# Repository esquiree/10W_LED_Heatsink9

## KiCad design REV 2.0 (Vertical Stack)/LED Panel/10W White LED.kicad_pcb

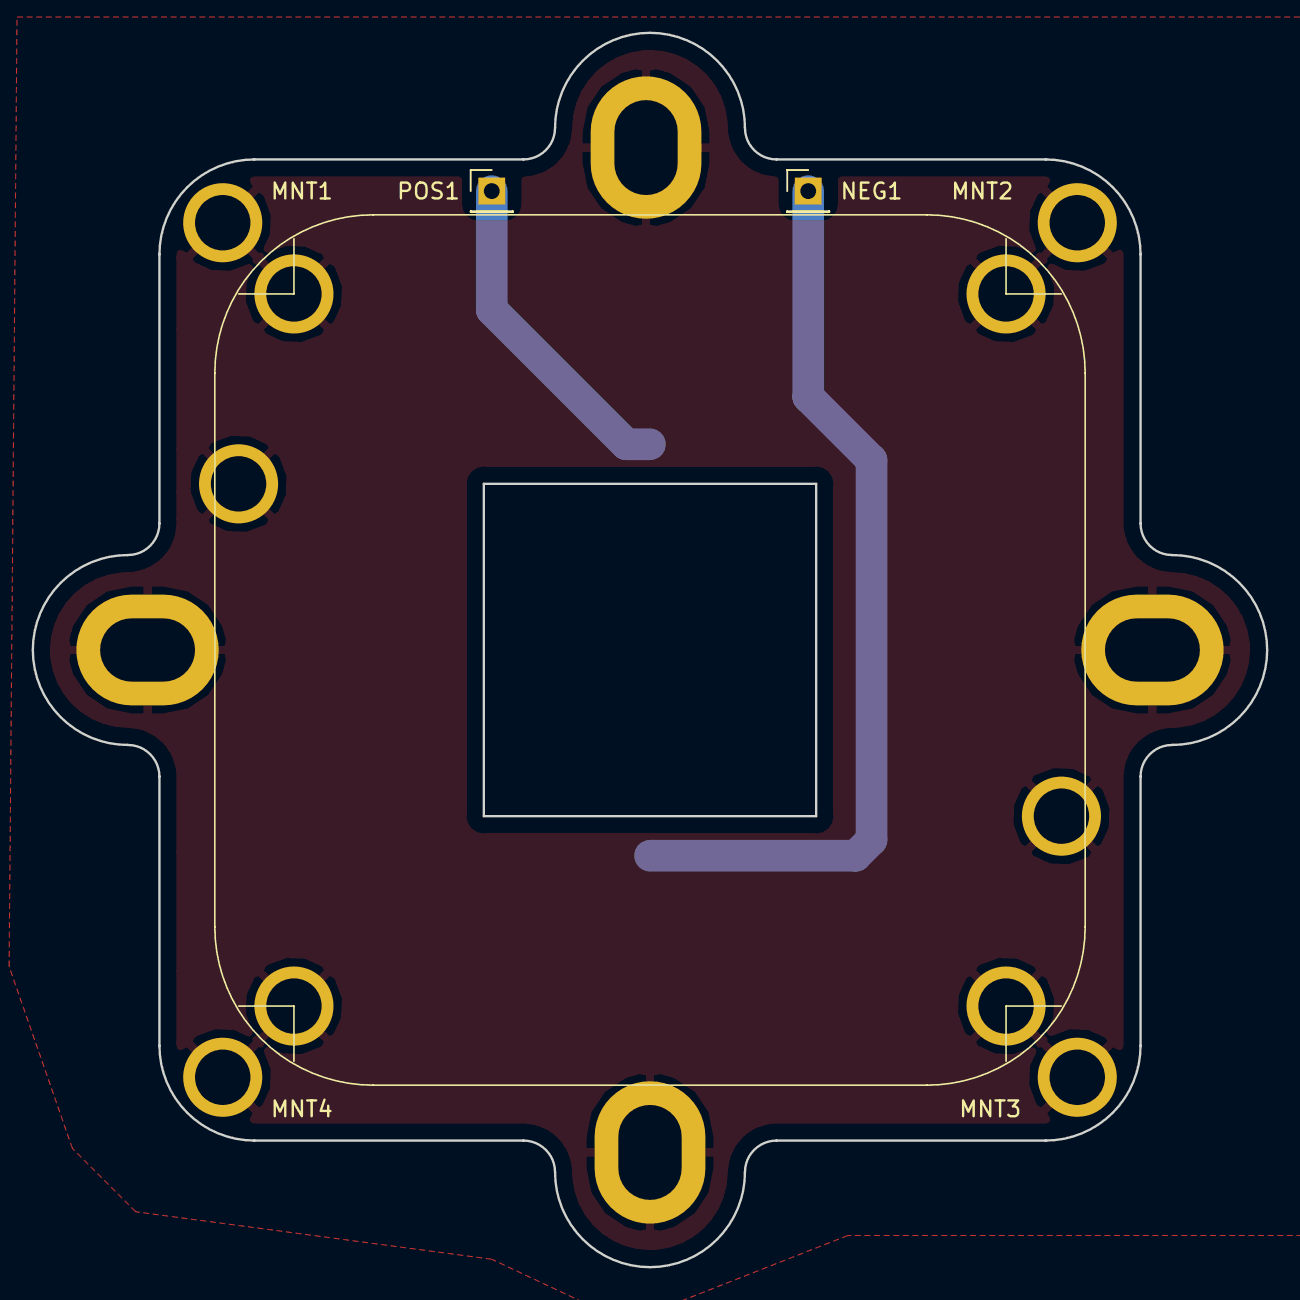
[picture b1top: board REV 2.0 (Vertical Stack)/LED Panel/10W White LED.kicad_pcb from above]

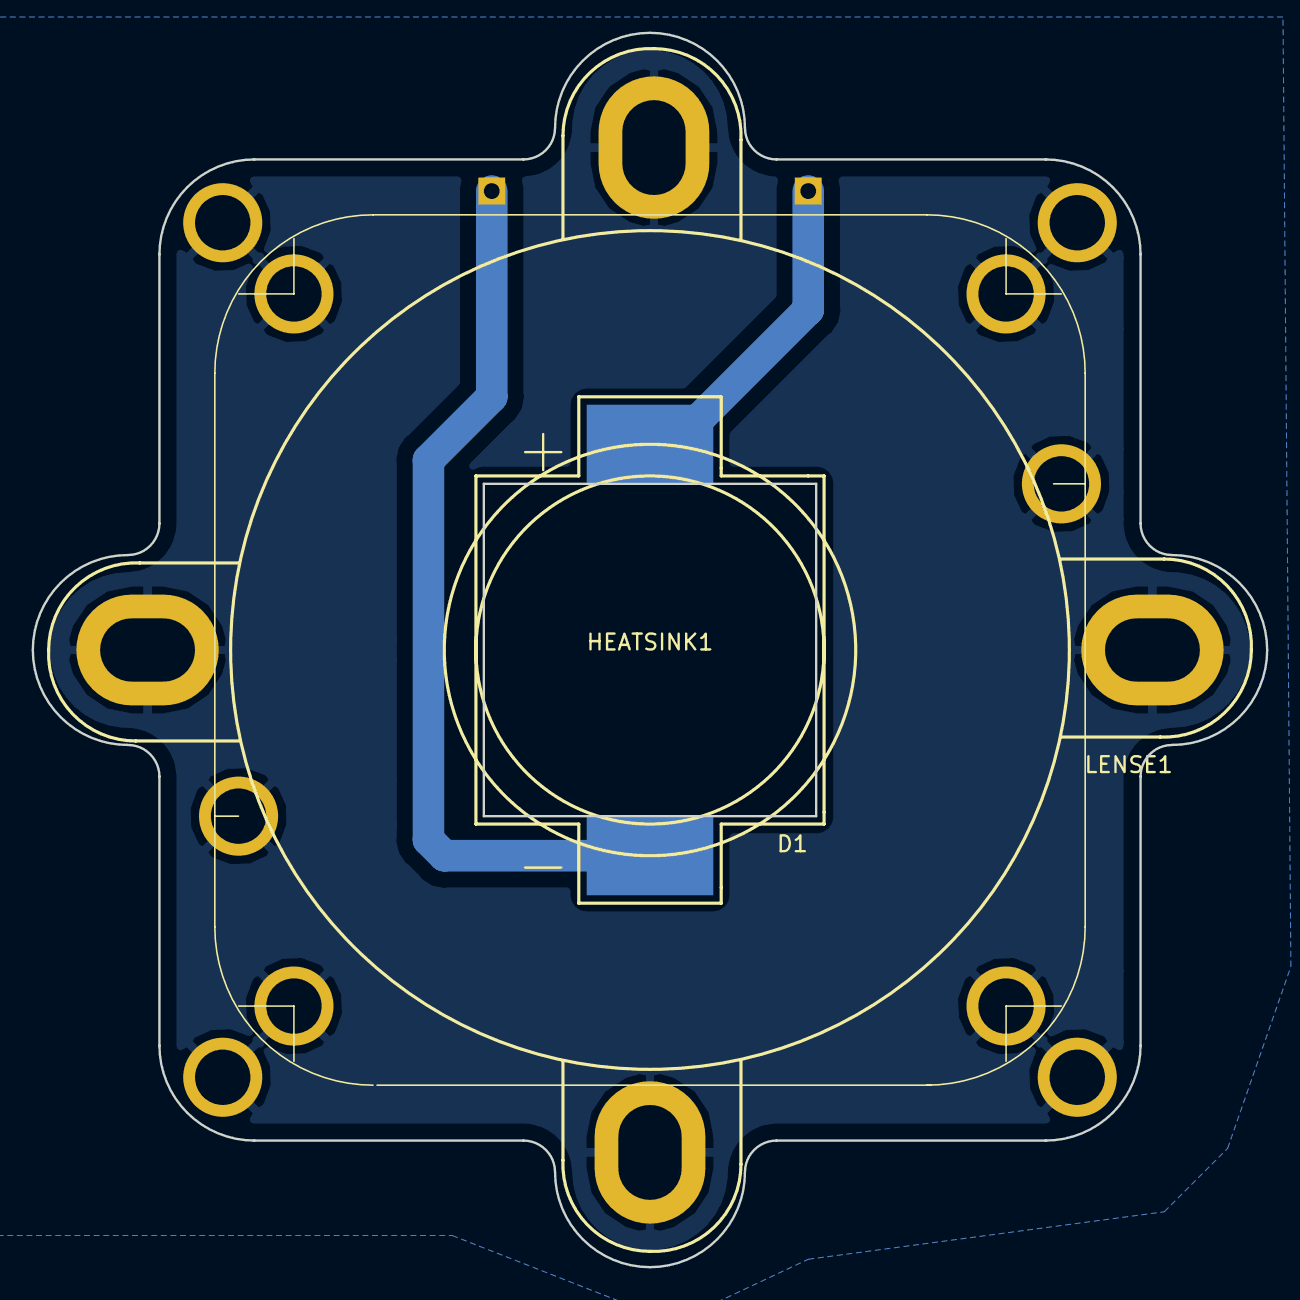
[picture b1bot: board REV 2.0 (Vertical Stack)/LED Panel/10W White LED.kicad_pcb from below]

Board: 2 copper layers, 78.0 x 78.0 mm, 9 parts (3 on the bottom side), 3 nets.

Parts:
D1: LED; 10W_LED
HEATSINK1: Conn_01x02; 55mm_heatsink
LENSE1: Conn_01x02; LED_Lense
MNT1, MNT2, MNT3, MNT4: Conn_01x02; 4mm Mount
NEG1: Conn_01x02; Pin_Header_Straight_1x01_Pitch2.54mm
POS1: Conn_01x02; Pin_Header_Straight_1x01_Pitch2.54mm

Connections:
GND: HEATSINK1.1, HEATSINK1.2, HEATSINK1.3, LENSE1.1, MNT1.1, MNT2.1, MNT3.1, MNT4.1
unnamed: D1.1, NEG1.1
unnamed: D1.2, POS1.1

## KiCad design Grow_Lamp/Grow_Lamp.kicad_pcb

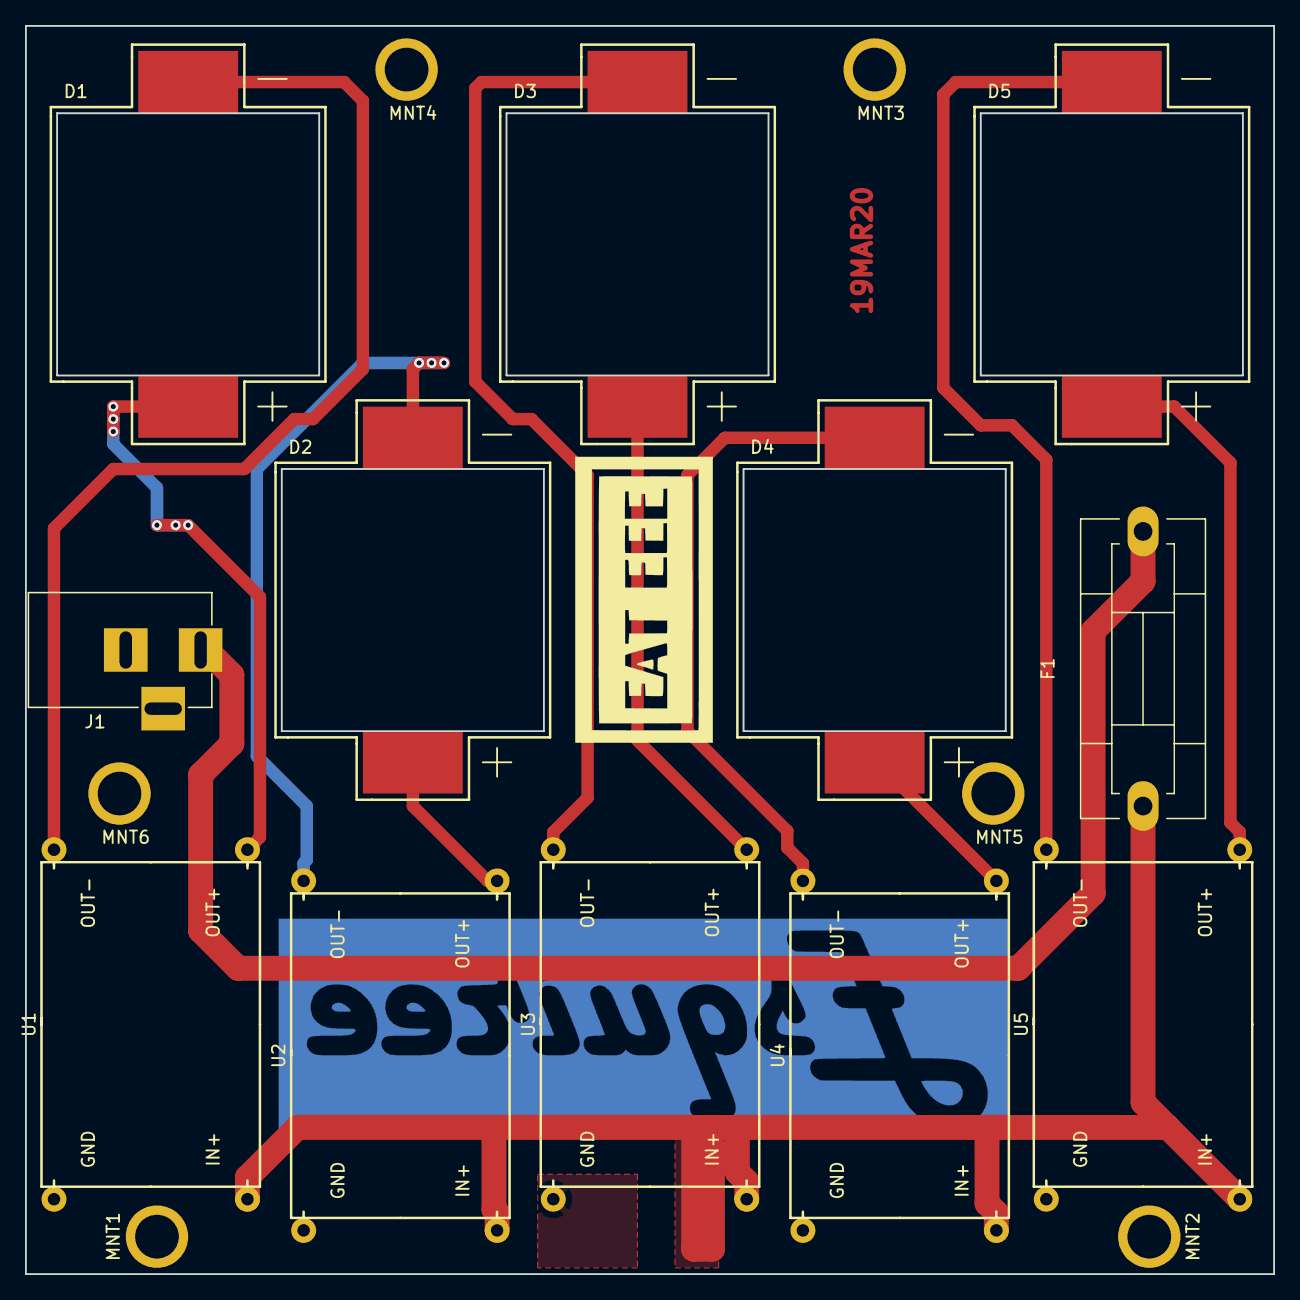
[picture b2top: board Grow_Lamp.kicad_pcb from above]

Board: 2 copper layers, 100.0 x 100.0 mm, 18 parts (0 on the bottom side), 13 nets.

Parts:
D1, D2, D3, D4, D5: LED; 10W_LED
F1: Fuse; Fuseholder5x20_horiz_SemiClosed_Casing10x25mm
J1: Barrel_Jack; BARREL_JACK
MNT1, MNT2, MNT3, MNT4, MNT5, MNT6: Conn_01x01; 4mm Mount
U1, U2, U3, U4, U5: 10W_LED_DRIVER; 10W_LED_Driver

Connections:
+12V: F1.1, U1.2, U2.2, U3.2, U4.2, U5.2
GND: J1.2, MNT1.1, MNT2.1, MNT3.1, MNT4.1, MNT5.1, MNT6.1, U1.1, U2.1, U3.1, U4.1, U5.1
unnamed: D1.1, U1.4
unnamed: D1.2, U1.3
unnamed: D2.1, U2.4
unnamed: D2.2, U2.3
unnamed: D3.1, U3.4
unnamed: D3.2, U3.3
unnamed: D4.1, U4.4
unnamed: D4.2, U4.3
unnamed: D5.1, U5.4
unnamed: D5.2, U5.3
unnamed: F1.2, J1.1

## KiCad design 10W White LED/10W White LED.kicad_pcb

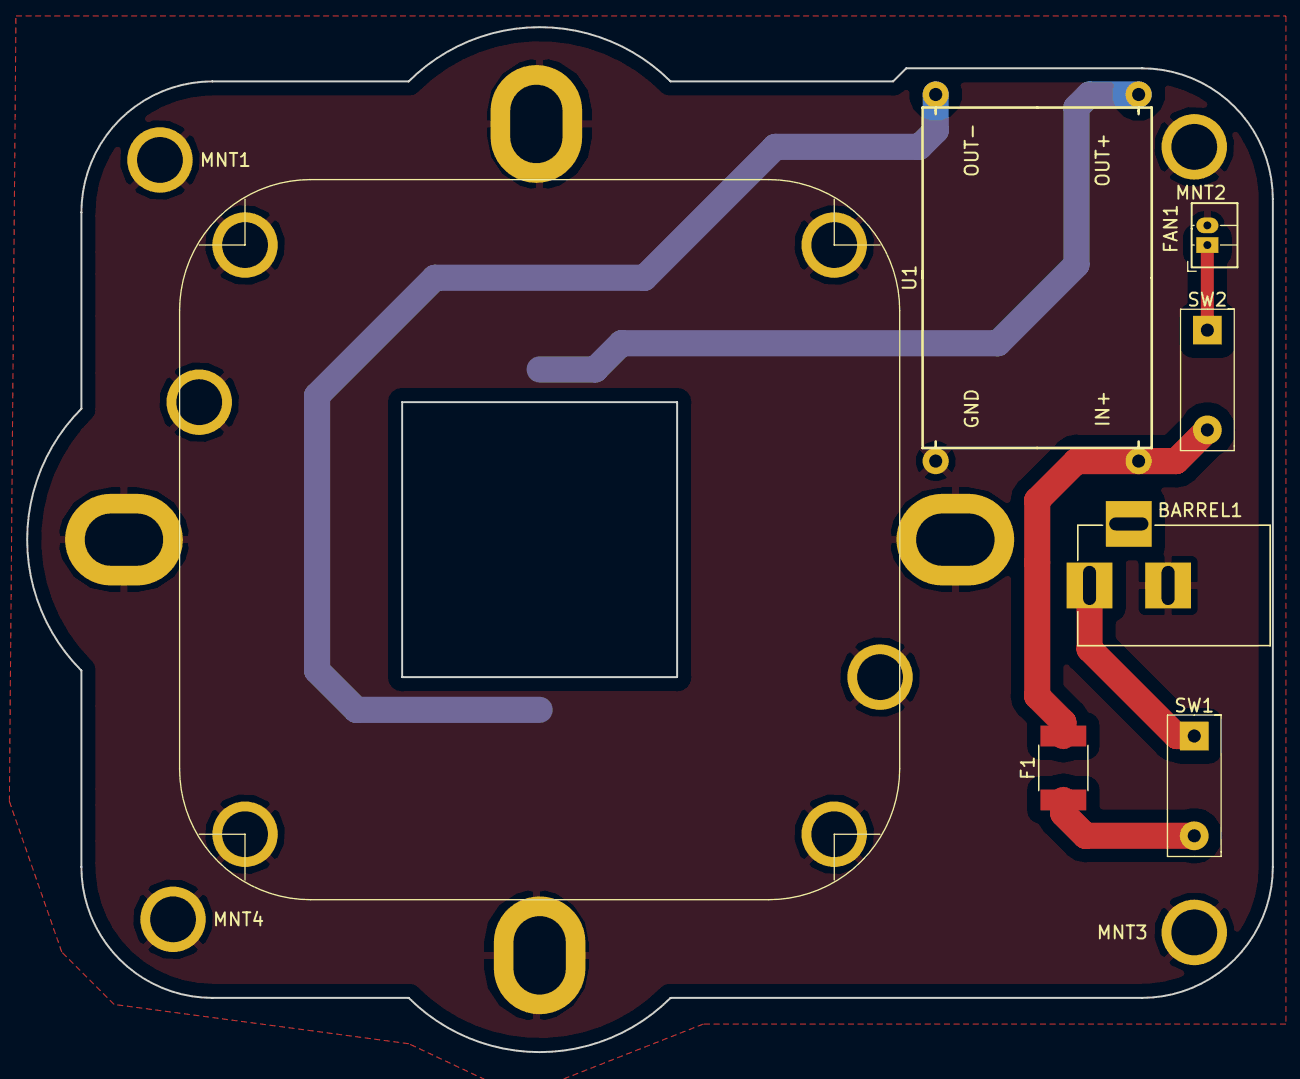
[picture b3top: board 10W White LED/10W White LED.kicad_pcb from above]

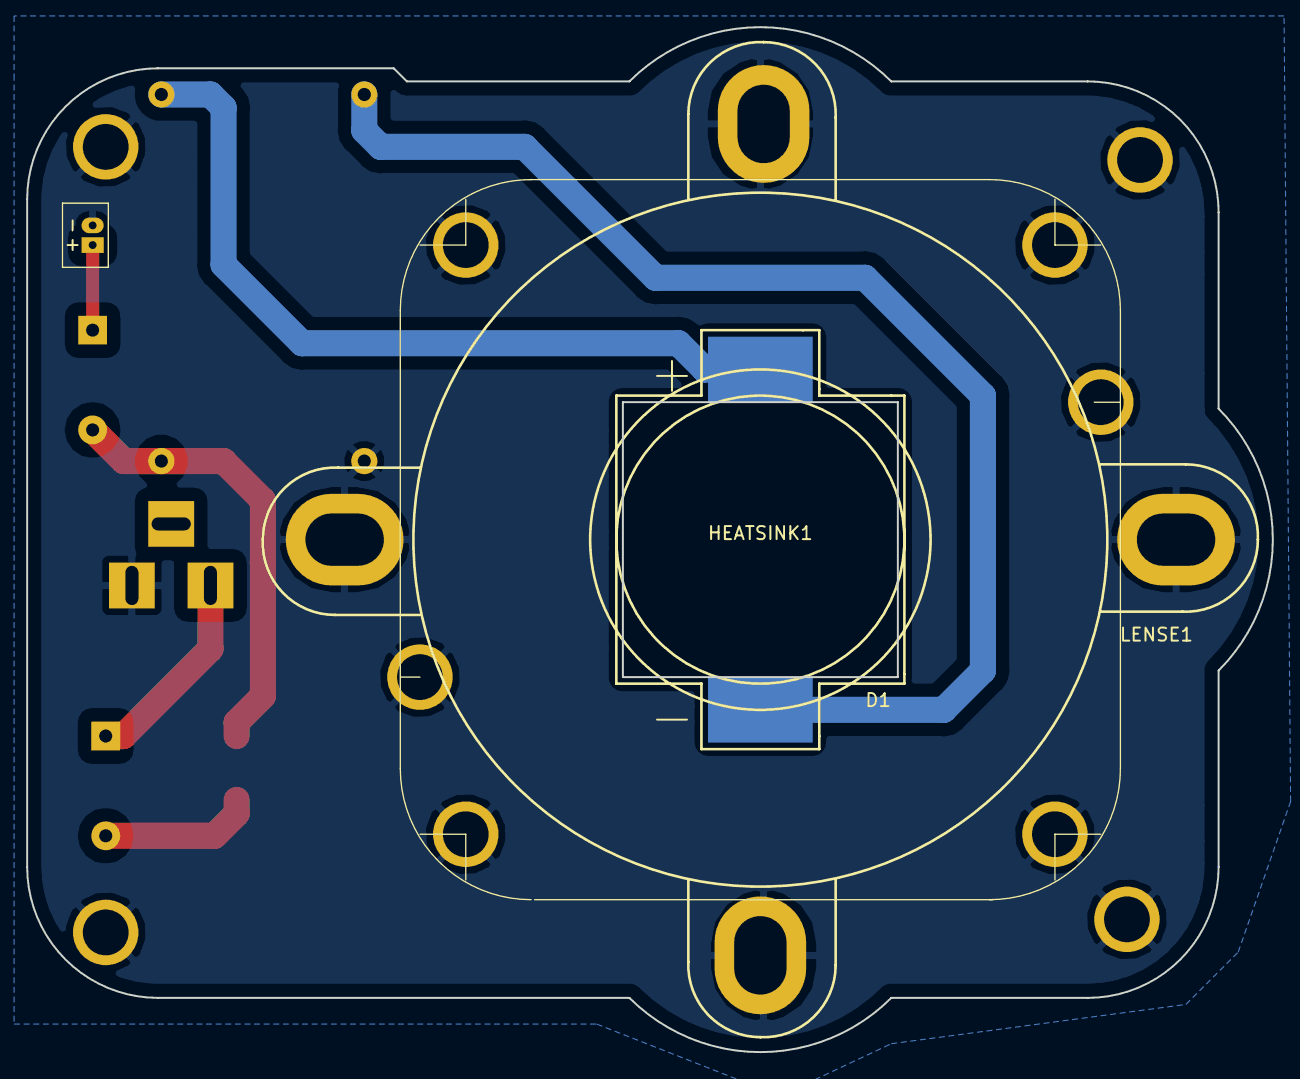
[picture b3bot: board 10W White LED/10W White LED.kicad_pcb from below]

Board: 2 copper layers, 95.1 x 78.3 mm, 13 parts (3 on the bottom side), 7 nets.

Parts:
BARREL1: Barrel_Jack; BARREL_JACK
D1: LED; 10W_LED
F1: Fuse; R_1812
FAN1: Conn_01x02; 1_5MM ZH JST
HEATSINK1: Conn_01x02; 55mm_heatsink
LENSE1: Conn_01x02; LED_Lense
MNT1, MNT2, MNT3, MNT4: Conn_01x02; 4mm Mount
SW1, SW2: SW_SPST; Single Dip Siwtch
U1: 10W_LED_DRIVER; 10W_LED_Driver

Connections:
+12V: F1.2, SW2.2, U1.2
GND: BARREL1.2, FAN1.2, HEATSINK1.1, HEATSINK1.2, HEATSINK1.3, LENSE1.1, MNT1.1, MNT2.1, MNT3.1, MNT4.1, U1.1
unnamed: BARREL1.1, SW1.1
unnamed: D1.1, U1.4
unnamed: D1.2, U1.3
unnamed: F1.1, SW1.2
unnamed: FAN1.1, SW2.1

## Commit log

2019-12-07 initial push. rev 1.0
